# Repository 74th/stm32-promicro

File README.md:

# STM32 ProMicro size Board

- STM32F103 -> see [x32micro](https://github.com/74th/x32promicro)
- [STM32G030F6P4](stm32g03xfxp)
- [STM32G431C8U6](stm32g431cxux)

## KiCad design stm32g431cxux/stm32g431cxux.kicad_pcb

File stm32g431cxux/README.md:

# STM32G431CxUx ProMicro

## v1.1.0

### Documents

- semantics [PDF](./stm32g431-promicro-v1.1.0.pdf) [kicanvas](https://kicanvas.org/?github=https%3A%2F%2Fgithub.com%2F74th%2Fstm32-promicro%2Fblob%2Fstm32g431cxux%2F1.1.0%2Fstm32g431cxux%2Fstm32g431cxux.kicad_sch)
- pcb [kicanvas](https://kicanvas.org/?github=https%3A%2F%2Fgithub.com%2F74th%2Fstm32-promicro%2Fblob%2Fstm32g431cxux%2F1.1.0%2Fstm32g431cxux%2Fstm32g431cxux.kicad_pcd)

### Pin Map

### errorta

- Silk on board has F0 and F1 reversed. ボード上のシルクに F0 と F1 が逆になっています。

### BOM

| Reference | Name                              | Quantity |
| --------- | --------------------------------- | -------- |
| C1, C2    | Capacitor 0603 10uF               | 2        |
| C3-C6     | Capacitor 0603 100nF              | 4        |
| D1        | LED 0805 Blue                     | 1        |
| F1        | PolyFuse 1206 Polyfuse            | 1        |
| J1        | USB Type-C Receptacle             | 1        |
| J2        | Box Pin Header 2x5 Pitch 1.27mm   | 1        |
| R1, R2    | Register 0603 5.1kΩ               | 2        |
| R3-R5     | Register 0603 10kΩ                | 3        |
| SW1       | Button SKRPABE010                 | 1        |
| U1        | Regulator 3.3V SOT-89 AMS1117-3.3 | 1        |
| U2        | MCU UFQFPN48 ST STM32G431CBUx     | 1        |

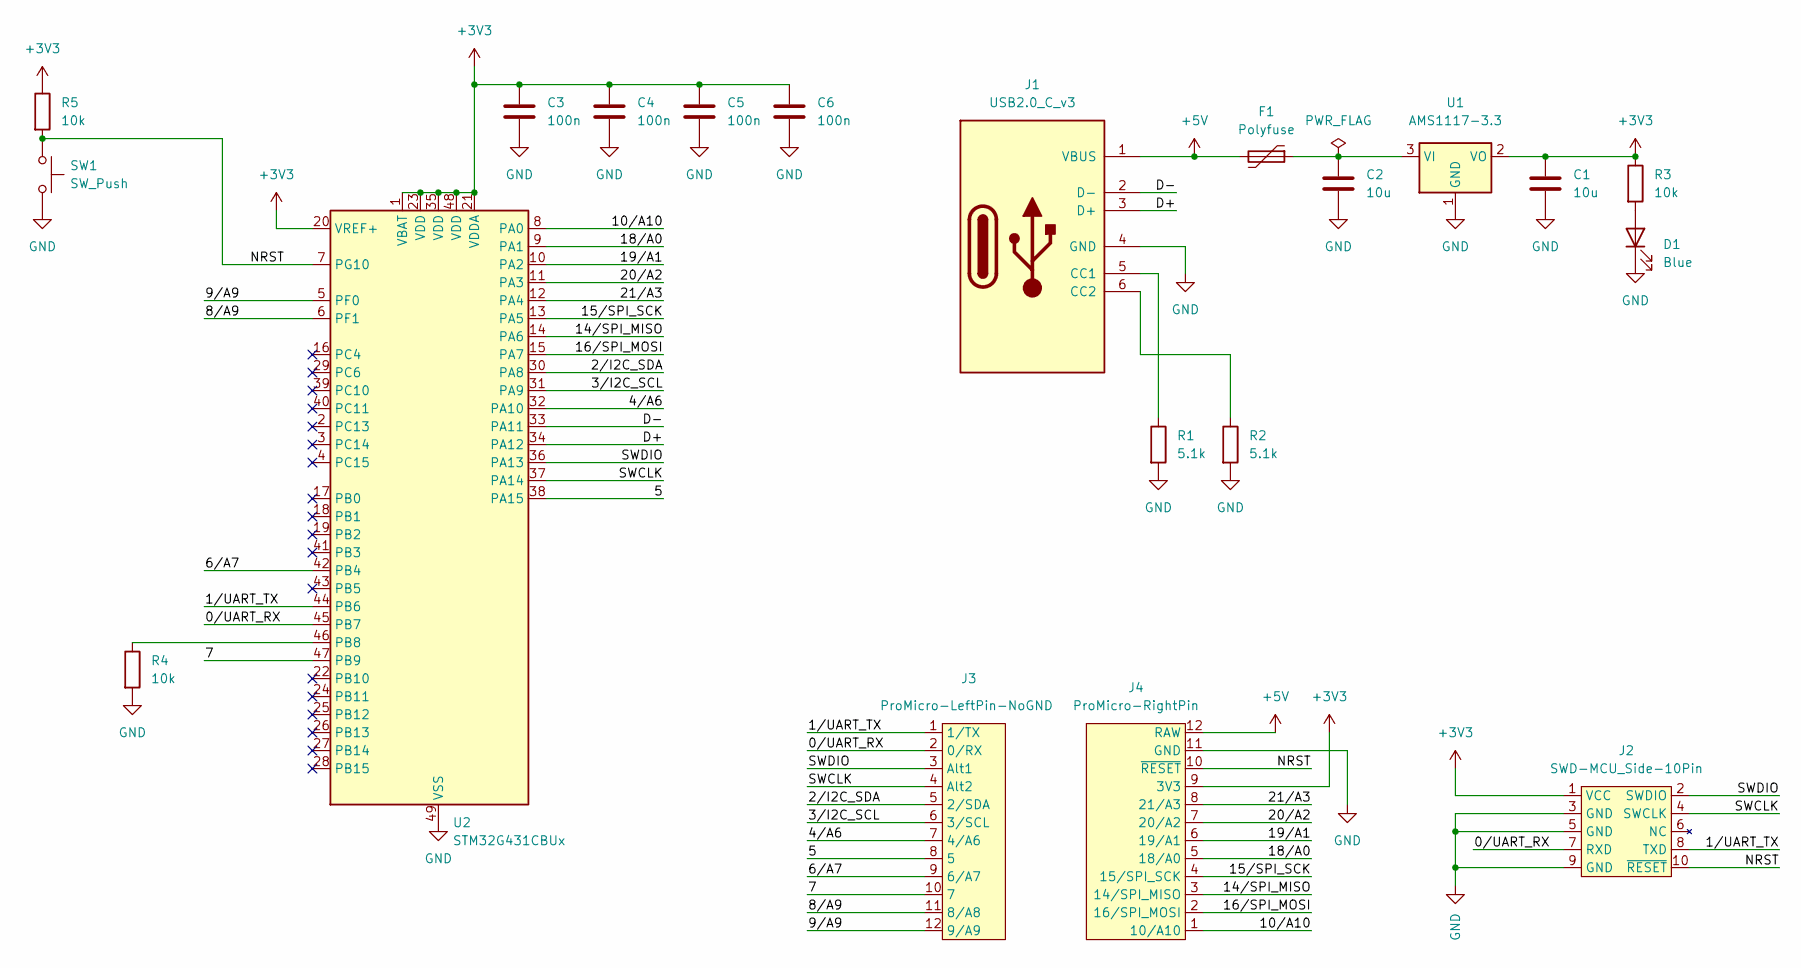
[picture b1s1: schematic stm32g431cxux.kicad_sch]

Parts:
C1, C2: 10u; Capacitor_0603_1608
C3, C4, C5, C6: 100n; Capacitor_0603_1608
D1: Blue; LED_0805_2012Metric_Pad1.15x1.40mm_HandSolder
F1: Polyfuse; Fuse_1206_3216Metric
J1: USB2.0_C_v3; USB-C-12-Pin-SMD
J2: SWD-MCU_Side-10Pin; SWD_2x05_P1.27mm
J3: ProMicro-LeftPin-NoGND; ProMicro_LIKE_LEFT_NO_GND
J4: ProMicro-RightPin; ProMicro_LIKE_RIGHT
R1, R2: 5.1k; Register_0603_1608
R3, R4, R5: 10k; Register_0603_1608
SW1: SW_Push; SKRPABE010
U1: AMS1117-3.3; SOT-89-3_Handsoldering
U2: STM32G431CBUx; QFN-48-1EP_7x7mm_P0.5mm_EP5.6x5.6mm

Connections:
+3V3: C1.1, C3.1, C4.1, C5.1, C6.1, J2.1 (VCC), J4.9 (3V3), R3.1, R5.1, U1.2 (VO), U2.1 (VBAT), U2.20 (VREF+), U2.21 (VDDA), U2.23 (VDD), U2.35 (VDD), U2.48 (VDD)
+5V: F1.2, J1.1 (VBUS), J4.12 (RAW)
/0/UART_RX: J2.7 (RXD), J3.2 (0/RX), U2.45 (PB7)
/1/UART_TX: J2.8 (TXD), J3.1 (1/TX), U2.44 (PB6)
/2/I2C_SDA: J3.5 (2/SDA), U2.30 (PA8)
/3/I2C_SCL: J3.6 (3/SCL), U2.31 (PA9)
/4/A6: J3.7 (4/A6), U2.32 (PA10)
/5: J3.8 (5), U2.38 (PA15)
/6/A7: J3.9 (6/A7), U2.42 (PB4)
/7: J3.10 (7), U2.47 (PB9)
/8/A9: J3.11 (8/A8), U2.6 (PF1)
/9/A9: J3.12 (9/A9), U2.5 (PF0)
/10/A10: J4.1 (10/A10), U2.8 (PA0)
/14/SPI_MISO: J4.3 (14/SPI_MISO), U2.14 (PA6)
/15/SPI_SCK: J4.4 (15/SPI_SCK), U2.13 (PA5)
/16/SPI_MOSI: J4.2 (16/SPI_MOSI), U2.15 (PA7)
/18/A0: J4.5 (18/A0), U2.9 (PA1)
/19/A1: J4.6 (19/A1), U2.10 (PA2)
/20/A2: J4.7 (20/A2), U2.11 (PA3)
/21/A3: J4.8 (21/A3), U2.12 (PA4)
/D+: J1.3 (D+), U2.34 (PA12)
/D-: J1.2 (D-), U2.33 (PA11)
/NRST: J2.10 (~RESET), J4.10 (~RESET), R5.2, SW1.1, U2.7 (PG10)
/SWCLK: J2.4 (SWCLK), J3.4 (Alt2), U2.37 (PA14)
/SWDIO: J2.2 (SWDIO), J3.3 (Alt1), U2.36 (PA13)
GND: C1.2, C2.2, C3.2, C4.2, C5.2, C6.2, D1.1 (K), J1.4 (GND), J2.3 (GND), J2.5 (GND), J2.9 (GND), J4.11 (GND), R1.2, R2.2, R4.2, SW1.2, U1.1 (GND), U2.49 (VSS)
unnamed: D1.2 (A), R3.2
unnamed: J1.5 (CC1), R1.1
unnamed: J1.6 (CC2), R2.1
unnamed: C2.1, F1.1, U1.3 (VI)
unnamed: R4.1, U2.46 (PB8)

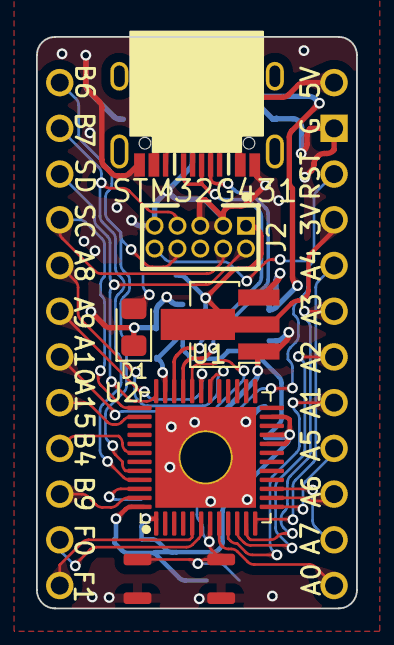
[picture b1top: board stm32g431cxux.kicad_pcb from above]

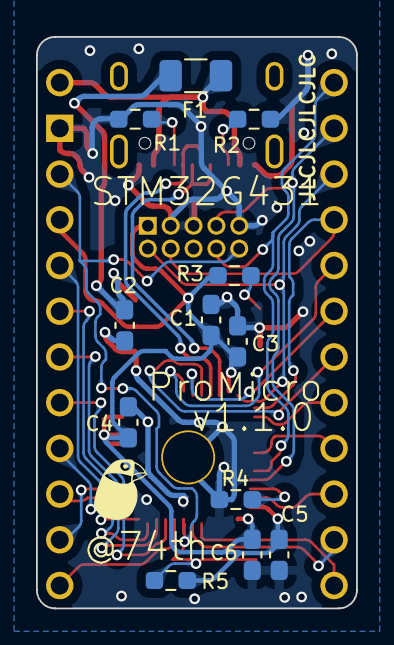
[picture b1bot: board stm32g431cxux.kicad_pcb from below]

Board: 2 copper layers, 17.8 x 31.8 mm, 20 parts (12 on the bottom side), 31 nets.

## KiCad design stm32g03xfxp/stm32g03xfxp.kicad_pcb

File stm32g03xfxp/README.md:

# STM32F03xfxp ProMicro

## v1.3.0

- change SWD port to 10 Pin with UART like Arduino UNO R4 (but, vcc is 3.3V)

### Documents

- Semantics 回路図 [PDF](stm32g03xfxp-semantcs-v1.3.0.pdf) [kicanvas](https://kicanvas.org/?github=https%3A%2F%2Fgithub.com%2F74th%2Fstm32-promicro%2Fblob%2Fstm32g03xfxp%2Fv1.3.0%2Fstm32g03xfxp%2Fstm32g03xfxp.kicad_sch)
- PCB [kicanvas](https://kicanvas.org/?github=https%3A%2F%2Fgithub.com%2F74th%2Fstm32-promicro%2Fblob%2Fmain%2Fstm32g03xfxp%2Fstm32g03xfxp.kicad_pcb)

### Debug Port

The box pin header for SWD has the following pin layout.

SWD のピンヘッダは以下のピン配置になっています。

## Pinout

For other functions, please refer to the datasheet.

他の機能はデータシートを参照ください。

### BOM

| Reference | Name                              | Quantity |
| --------- | --------------------------------- | -------- |
| C1        | Capacitor 0805 10uF               | 1        |
| C2        | Capacitor 0805 2.2uF              | 1        |
| C3, C4    | Capacitor 0805 100nF              | 2        |
| D1        | LED 0805 Blue                     | 1        |
| J1        | USB Type-C Receptacle             | 1        |
| J2        | Pin Header 2x5 Pitch 1.27mm (SWD) | 1        |
| R1, R2    | Register 0805 5.1kΩ               | 2        |
| R3, R4    | Register 0805 10kΩ                | 2        |
| SW1       | Button SKRPABE010                 | 1        |
| U1        | Regulator 3.3V SOT-89 AMS1117     | 1        |
| U2        | MCU ST STM32G030F6Px              | 1        |

## v1.2.0

### Documents

- Semantics 回路図 [PDF](stm32g03xfxp-semantcs-v1.2.0.pdf) [kicanvas](https://kicanvas.org/?github=https%3A%2F%2Fgithub.com%2F74th%2Fstm32-promicro%2Fblob%2Fstm32g03xfxp%2Fv1.2.0%2Fstm32g03xfxp%2Fstm32g03xfxp.kicad_sch)
- PCB [PDF](stm32g03xfxp-pcb.pdf) [kicanvas](https://kicanvas.org/?github=https%3A%2F%2Fgithub.com%2F74th%2Fstm32-promicro%2Fblob%2Fstm32g03xfxp%2Fv1.2.0%2Fstm32g03xfxp%2Fstm32g03xfxp.kicad_pcb)

### Debug Port

The box pin header for DAP Link has the following pin layout.

DAP Link 用のボックスピンヘッダは以下のピン配置になっています。

### Pinout

For other functions, please refer to the datasheet.

他の機能はデータシートを参照ください。

### BOM

| id    | parts name                                  | num |
| ----- | ------------------------------------------- | --- |
| J1    | USB 2.0 Type-C Socket (Only Power)          | 1   |
| R1,R2 | 0806 Register 5.1k                          | 2   |
| R4    | 0806 Register 0                             | 1   |
| R3,R6 | 0806 Register 10k                           | 2   |
| C1    | 0806 Capacitor 10u                          | 1   |
| C2    | 0806 Capacitor 2.2u                         | 1   |
| C3,C4 | 0806 Capacitor 100n                         | 2   |
| U2    | TSSOP-20 MCU STM32G030F6Px                  | 1   |
| D1    | 0805 LED Blue                               | 1   |
| U1    | SOT-89 3.3V Regulator AMS1117-3.3           | 1   |
| SW1   | SKRPABE010 Push Switch                      | 1   |
| CH3   | Pitch 1.25mm 2x3 Box Pin Header DAPLink-SWD | 1   |

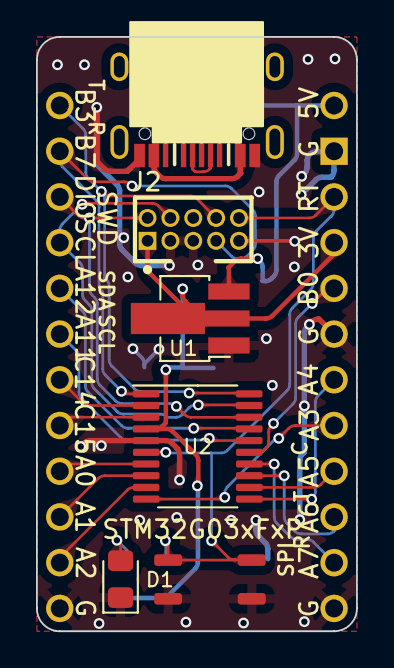
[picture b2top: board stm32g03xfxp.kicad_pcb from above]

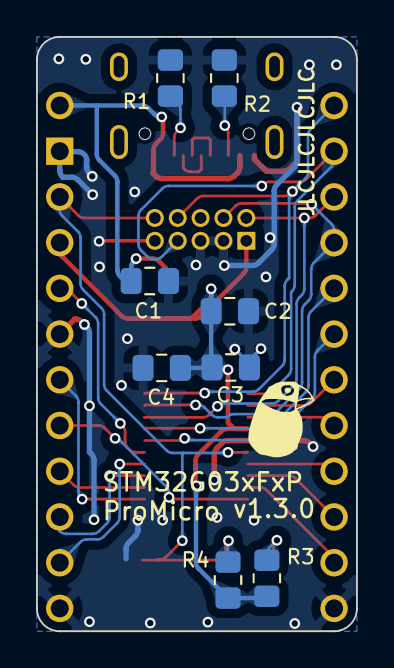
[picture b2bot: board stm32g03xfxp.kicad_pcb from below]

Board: 2 copper layers, 17.8 x 33.0 mm, 17 parts (9 on the bottom side), 24 nets.

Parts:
C1: 10u; Capacitor_0805_2012
C2: 2.2u; Capacitor_0805_2012
C3, C4: 100n; Capacitor_0805_2012
CH1: ProMicro-LeftPin; ProMicro_LIKE_LEFT_NO_GND
CH2: ProMicro-RightPin; ProMicro_LIKE_RIGHT
D1: Blue; LED_0805_2012Metric_Pad1.15x1.40mm_HandSolder
G1: LOGO; 74th-5mm
J1: USB2.0_C_v3; USB-C-12-Pin-SMD
J2: SWD-MCU_Side-10Pin; SWD_2x05_P1.27mm
R1, R2: 5.1k; Register_0805_2012
R3, R4: 10k; Register_0805_2012
SW1: SW_Push; SKRPABE010
U1: AMS1117-3.3; Regulator_AMS1117_SOT-89
U2: STM32G030F6Px; TSSOP-20_4.4x6.5mm_P0.65mm

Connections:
+3V3: C2.1, C3.1, C4.1, CH2.9 (3V3), J2.1 (VCC), R3.1, R4.1, U1.2 (VO), U2.4 (VDD)
+5V: C1.1, CH2.12 (RAW), J1.1 (VBUS), U1.3 (VI)
/0/UART_RX: CH1.2 (0/RX), J2.7 (RXD), U2.1 (PB7/PB8)
/1/UART_TX: CH1.1 (1/TX), J2.8 (TXD), U2.20 (PB3/PB4/PB5/PB6)
/2/I2C_SDA: CH1.5 (2/SDA), U2.17 (PA12/PA10)
/3/I2C_SCL: CH1.6 (3/SCL), U2.16 (PA11/PA9)
/4/A6: CH1.7 (4/A6), U2.2 (PC14/PB9)
/5: CH1.8 (5), U2.3 (PC15)
/6/A7: CH1.9 (6/A7), U2.7 (PA0)
/7: CH1.10 (7), U2.8 (PA1)
/8/A8: CH1.11 (8/A8), U2.9 (PA2)
/14/API_MISO: CH2.3 (14/SPI_MISO), U2.13 (PA6)
/15/SPI_SCK: CH2.4 (15/SPI_SCK), U2.12 (PA5)
/16/SPI_MOSI: CH2.2 (16/SPI_MOSI), U2.14 (PA7)
/18/A0: CH2.5 (18/A0), U2.10 (PA3)
/19/A1: CH2.6 (19/A1), U2.11 (PA4)
/21/A3: CH2.8 (21/A3), U2.15 (PB0/PB1/PB2/PA8)
/RST: CH2.10 (~RESET), J2.10 (~RESET), R4.2, SW1.2, U2.6 (NRST)
/SWCLK: CH1.4 (Alt2), J2.4 (SWCLK), U2.19 (PA14/PA15)
/SWDIO: CH1.3 (Alt1), J2.2 (SWDIO), U2.18 (PA13)
GND: C1.2, C2.2, C3.2, C4.2, CH1.12 (9/A9), CH2.1 (10/A10), CH2.7 (20/A2), CH2.11 (GND), D1.1 (K), J1.4 (GND), J2.3 (GND), J2.5 (GND), J2.9 (GND), R1.2, R2.2, SW1.1, U1.1 (GND), U2.5 (VSS)
unnamed: D1.2 (A), R3.2
unnamed: J1.5 (CC1), R1.1
unnamed: J1.6 (CC2), R2.1

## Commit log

2023-04-08 before routing
2023-04-08 stm32g03xfxp/v1.0.0
2023-04-19 fix dio/clk
2023-04-29 v1.1.1
2023-04-30 v1.2.0
2023-06-18 before free routing
2023-06-18 after free routing
2023-07-13 stm32g03xfxp/v1.2.0
2023-08-20 stm32g03xfxp/v1.3.0
2023-10-06 update metadata
2023-10-06 update semantics
2023-10-07 add pinmap
